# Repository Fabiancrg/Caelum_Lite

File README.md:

| Supported Targets | ESP32-C6 | ESP32-H2 |
| ----------------- |  -------- | -------- |

# Caelum - Zigbee Weather Station

## Project Description

This project implements a battery-powered environmental monitoring device using ESP32-C6/H2 with Zigbee connectivity. The device features a 3-endpoint design with remote sleep configuration, optimized for low-power operation with deep sleep support and extended wake time during network join.

This project is based on the examples provided in the ESP Zigbee SDK:

* [ESP Zigbee SDK Docs](https://docs.espressif.com/projects/esp-zigbee-sdk)
* [ESP Zigbee SDK Repo](https://github.com/espressif/esp-zigbee-sdk)

## Device Features

### 🌐 Zigbee Endpoints Overview

| Endpoint | Device Type | Clusters | Description |
|----------|-------------|----------|-------------|
| **1** | Environmental Sensor | Temperature, Humidity, Pressure | BME280 sensor via I2C |
| **2** | Rain Gauge | Analog Input | Tipping bucket rain sensor with rainfall totals |
| **3** | Sleep Configuration | Analog Input | Remote sleep duration control (60-7200 seconds) |

### 📋 Detailed Endpoint Descriptions

#### **Endpoint 1: Environmental Monitoring & Power Management**
- **Hardware**: BME280 sensor via I2C
  - **ESP32-H2**: SDA: GPIO10, SCL: GPIO11
  - **ESP32-C6**: SDA: GPIO6, SCL: GPIO7
- **Measurements**: 
  - 🌡️ **Temperature**: -40°C to +85°C (±1°C accuracy)
  - 💧 **Humidity**: 0-100% RH (±3% accuracy) 
  - 🌪️ **Pressure**: 300-1100 hPa (±1 hPa accuracy)
  - 🔋 **Battery Monitoring**: Li-Ion voltage (2.7V-4.2V) and percentage
- **Battery Monitoring**:
  - **Hardware**: GPIO4 (ADC1_CH4) with voltage divider (2x 100kΩ resistors)
  - **Voltage**: Real-time battery voltage in 0.1V units
  - **Percentage**: Battery level 0-100% based on Li-Ion discharge curve
  - **Calibration**: ESP32-H2 ADC correction factor (1.604x) for accurate readings
  - **Power Configuration Cluster**: Standard Zigbee battery attributes
- **Features**: Automatic reporting during wake cycles, Zigbee-standard units
- **Use Case**: Weather monitoring, HVAC automation, air quality tracking, battery-powered applications

#### **Endpoint 2: Rain Gauge System**
- **Hardware**: Tipping bucket rain gauge with reed switch
  - **ESP32-H2**: GPIO12 (RTC-capable for sleep wake-up)
  - **ESP32-C6**: GPIO5 (RTC-capable for sleep wake-up)
- **Measurements**: Cumulative rainfall in millimeters (0.36mm per tip)
- **Features**: 
  - Advanced debouncing (200ms + 1000ms bounce settle)
  - Persistent storage (NVS) for total tracking
  - Smart reporting (1mm threshold OR hourly)
  - Network-aware operation (only active when connected)
  - **Both targets**: Wake from deep sleep on rain detection
- **Specifications**: 
  - Maximum rate: 200mm/hour supported
  - Accuracy: ±0.36mm per bucket tip
  - Storage: Non-volatile total persistence across reboots
- **Use Case**: Weather station, irrigation control, flood monitoring

#### **Endpoint 3: Sleep Configuration**
- **Hardware**: Software-only (virtual endpoint)
- **Control**: Sleep duration in seconds (60-7200s range)
- **Features**:
  - Remote configuration via Zigbee2MQTT or Home Assistant
  - Persistent storage (NVS) - survives reboots
  - Real-time updates - changes apply on next wake cycle
  - Default: 900 seconds (15 minutes)
- **Use Case**: 
  - Battery optimization (longer intervals = longer battery life)
  - Seasonal adjustments (frequent updates in rainy season)
  - Dynamic power management based on weather conditions

### 🔧 Hardware Configuration

#### **Required Components**
- ESP32-C6 or ESP32-H2 development board
- BME280 environmental sensor module
- Tipping bucket rain gauge with reed switch
- Li-Ion battery (with protection circuit, 5V output recommended)
- Voltage divider (2x 100kΩ resistors for battery monitoring)
- Zigbee coordinator (ESP32-H2 or commercial gateway)

#### **Pin Assignments**

**ESP32-H2 (Recommended)**
```
GPIO 4  - Battery voltage input (ADC1_CH4 with voltage divider)
GPIO 10 - I2C SDA (BME280)
GPIO 11 - I2C SCL (BME280) 
GPIO 12 - Rain gauge input (RTC-capable)*
GPIO 9  - Built-in button (factory reset)
```

**ESP32-C6**
```
GPIO 4  - Battery voltage input (ADC1_CH4 with voltage divider)
GPIO 5  - Rain gauge input (RTC-capable)*
GPIO 6  - I2C SDA (BME280)
GPIO 7  - I2C SCL (BME280) 
GPIO 9  - Built-in button (factory reset)
```

*Both targets now use RTC-capable GPIO pins for rain detection during deep sleep

**Battery Voltage Divider Circuit**
```
Battery+ ──┬── 100kΩ ──┬── 100kΩ ── GND
           │           │
           │           └── GPIO4 (ADC input)
           │
           └── 5V output (to ESP32 power)
```
Note: Voltage divider monitors the cell voltage (2.7V-4.2V) while the battery pack provides 5V regulated output

### � Zigbee Integration
- **Protocol**: Zigbee 3.0  
- **Device Type**: End Device (sleepy end device for battery operation)
- **Supported Channels**: 11-26 (2.4 GHz)
- **Compatible**: Zigbee2MQTT, Home Assistant ZHA, Hubitat
- **OTA Support**: Over-the-air firmware updates enabled (see [OTA_GUIDE.md](OTA_GUIDE.md))

### ⚡ Power Management
- **Deep Sleep Mode**: Configurable intervals (60-7200 seconds, default 15 minutes)
  - **Configurable via Zigbee2MQTT**: Adjust sleep duration remotely from Home Assistant
  - **Connected**: Uses configured interval (default 15 minutes)
  - **Disconnected**: 30-second intervals for quick reconnection
  - **Max retries**: After 20 attempts (10 minutes), reduces to half configured duration
  - **Extended wake time**: Device stays awake for 60 seconds when not connected (instead of 10s) to allow Zigbee join process to complete
- **Wake-up Sources**:
  - Timer (configurable 60-7200 seconds)
  - **Rain detection during deep sleep** (both targets support RTC wake-up)
    - **ESP32-H2**: GPIO12 (RTC-capable)
    - **ESP32-C6**: GPIO5 (RTC-capable)
- **Network Retry Logic**: 
  - Prevents deep sleep when not connected to ensure reliable pairing
  - Extended 60-second wake period for join process completion
  - Connection success triggers 15-second reporting window before sleep
- **Battery Life**: Optimized for extended operation on battery power
- **Power Consumption**: ~100mA active, 7-10µA in deep sleep
- **Battery Estimate**: 3+ years with 2500mAh battery (15-minute intervals)

## 🚀 Quick Start

### Prerequisites

```bash
# Install ESP-IDF v5.5.1 or later
git clone -b v5.5.1 --recursive https://github.com/espressif/esp-idf.git
cd esp-idf
# For ESP32-H2 (recommended)
./install.sh esp32h2
# For ESP32-C6
./install.sh esp32c6
. ./export.sh
```

### Configure the Project
```bash
# For ESP32-H2 (recommended for better power management)
idf.py set-target esp32h2
# For ESP32-C6  
idf.py set-target esp32c6
idf.py menuconfig
```

### Build and Flash
```bash
# Erase previous data (recommended for first flash)
idf.py -p [PORT] erase-flash

# Build and flash the project
idf.py -p [PORT] flash monitor
```

### 🛠️ Configuration

### Device Operation

#### **Factory Reset**
- **Built-in Button (GPIO 9)**:
  - Long press (5s): Factory reset device

#### **Automatic Features**
- Environmental data reported during wake cycles
- Rain gauge totals stored persistently in NVS
- Smart rainfall reporting (1mm increments or hourly)
- Network connection status monitoring
- Deep sleep after data reporting (15-second window when connected, 60 seconds when not connected)
- Sleep duration remotely configurable via Zigbee2MQTT (60-7200 seconds)

### 📡 Data Reporting
- **Temperature/Humidity/Pressure**: Reported during wake cycles
- **Rainfall**: Immediate on tip detection (>1mm) or hourly
- **Sleep Duration**: Configurable 60-7200 seconds (default 15 minutes)
- **Sleep Cycle**: Configurable via Endpoint 3 for battery optimization

## 📊 Example Output

### Device Initialization
```
I (403) app_start: Starting scheduler on CPU0
I (408) WEATHER_STATION: Initialize Zigbee stack
I (558) WEATHER_STATION: Deferred driver initialization successful
I (568) WEATHER_STATION: BME280 sensor initialized successfully
I (578) WEATHER_STATION: Rain gauge initialized. Current total: 0.00 mm
I (578) WEATHER_STATION: Start network steering
```

### Network Connection
```
I (3558) WEATHER_STATION: Joined network successfully (Extended PAN ID: 74:4d:bd:ff:fe:63:f7:30, PAN ID: 0x13af, Channel:13, Short Address: 0x7c16)
I (3568) RAIN_GAUGE: Rain gauge enabled - device connected to Zigbee network
```

### Sensor Data Reporting
```
I (8000) WEATHER_STATION: 🌡️ Temperature: 22.35°C reported to Zigbee  
I (8010) WEATHER_STATION: 💧 Humidity: 45.20% reported to Zigbee
I (8020) WEATHER_STATION: 🌪️ Pressure: 1013.25 hPa reported to Zigbee
I (8030) BATTERY: 🔋 Li-Ion Battery: 4.17V (98%) - Zigbee values: 41 (0.1V), 196 (%*2)
I (8040) WEATHER_STATION: 📡 Temp: 22.4°C
I (8050) WEATHER_STATION: 📡 Humidity: 45.2%
I (8060) WEATHER_STATION: 📡 Pressure: 1013.3 hPa
```

### Rain Gauge Activity
```  
I (10000) RAIN_GAUGE: 🔍 Rain gauge interrupt received on GPIO18 (enabled: YES)
I (10010) RAIN_GAUGE: 🌧️ Rain pulse #1 detected! Total: 0.36 mm (+0.36 mm)
I (10020) RAIN_GAUGE: ✅ Rainfall total 0.36 mm reported to Zigbee
I (10030) WEATHER_STATION: 📡 Rain: 0.36 mm
```

### Deep Sleep Entry
```
I (18000) WEATHER_STATION: ⏳ Preparing for deep sleep...
I (18010) WEATHER_STATION: 💤 Entering deep sleep for 900 seconds (15 minutes)
```

## 🏠 Home Assistant Integration

When connected to Zigbee2MQTT or other Zigbee coordinators, the device appears as:

- **4x Sensor entities**: Temperature, Humidity, Pressure, Battery Percentage
- **1x Sensor entity**: Battery Voltage (mV)
- **1x Sensor entity**: Rainfall total with automatic updates
- **1x Number entity**: Sleep duration control (60-7200 seconds)

### Zigbee2MQTT Integration

A custom external converter is provided for full feature support with Zigbee2MQTT. See [ZIGBEE2MQTT_CONVERTER.md](ZIGBEE2MQTT_CONVERTER.md) for:
- Converter installation instructions
- Multi-endpoint support configuration
- Sleep duration control setup
- Home Assistant automation examples

### Device Information
- **Manufacturer**: ESPRESSIF
- **Model**: CAELUM-WS  
- **Firmware**: Configurable via CMakeLists.txt (default v0.1.0)
- **Supported**: Zigbee2MQTT with custom external converter

## 🔧 Configuration

Key parameters can be adjusted in `main/esp_zb_weather.h`:
- Default sleep duration: 900 seconds (15 minutes) - can be changed via Endpoint 3
- Sleep duration range: 60-7200 seconds (1 minute to 2 hours)
- Network retry interval: 30 seconds when disconnected
- Maximum connection retries: 20 attempts before reducing sleep interval
- Rain tip bucket volume: 0.36mm per tip
- Extended wake time: 60 seconds when not connected (for join process)

## 📝 Project Structure

```
WeatherStation/
├── main/
│   ├── esp_zb_weather.c     # Main Zigbee stack, 3-endpoint logic, network retry
│   ├── esp_zb_weather.h     # Configuration, endpoint definitions, firmware version
│   ├── esp_zb_ota.c         # OTA update implementation
│   ├── esp_zb_ota.h         # OTA interface
│   ├── sleep_manager.c      # Deep sleep management with RTC GPIO support
│   ├── sleep_manager.h      # Sleep manager interface
│   ├── bme280_app.c         # BME280 sensor driver with board-specific I2C
│   ├── bme280_app.h         # BME280 interface
│   ├── weather_driver.c     # DEPRECATED: Legacy driver (unused)
│   └── weather_driver.h     # DEPRECATED: Legacy interface (unused)
├── caelum-weather-station.js # Zigbee2MQTT external converter
├── CMakeLists.txt           # Build configuration with app_update dependency
├── partitions.csv           # Partition table with OTA support
├── sdkconfig.defaults       # Default SDK settings
├── OTA_GUIDE.md            # OTA update instructions
├── ZIGBEE2MQTT_CONVERTER.md # Zigbee2MQTT integration guide
├── DEEP_SLEEP_IMPLEMENTATION.md # Deep sleep implementation details
└── README.md               # This file
```

## 🔧 Troubleshooting

### Common Issues

#### **Rain Gauge Not Detecting**
- **ESP32-H2**: Verify GPIO12 connections and reed switch operation
- **ESP32-C6**: Verify GPIO5 connections and reed switch operation
- Check that device is connected to Zigbee network (rain gauge only active when connected)
- Ensure proper pull-down resistor on rain gauge input
- Both targets support rain detection during deep sleep

#### **BME280 Not Reading**  
- **ESP32-H2**: Check I2C connections (SDA: GPIO10, SCL: GPIO11)
- **ESP32-C6**: Check I2C connections (SDA: GPIO6, SCL: GPIO7)
- Verify BME280 I2C address (default: 0x76 or 0x77)
- Ensure proper power supply to sensor (3.3V)

#### **Battery Monitoring Issues**
- Verify voltage divider connections (2x 100kΩ resistors to GPIO4)
- Check battery cell voltage tap (should be 2.7V-4.2V at divider output)
- Ensure GPIO4 (ADC1_CH4) is properly configured
- Monitor serial output for ADC calibration messages
- **ESP32-H2 ADC quirk**: Uses empirical correction factor (1.604x) for DB_12 attenuation
- Battery percentage calculated from voltage (2.7V=0%, 4.2V=100%)

#### **Zigbee Connection Issues**
- Perform factory reset with long press (5s) on built-in button
- Ensure Zigbee coordinator is in pairing mode
- Check channel compatibility between coordinator and device
- **Auto-retry**: Device automatically retries every 30 seconds when disconnected
- **Extended wake time**: Device now stays awake for 60 seconds (instead of 10s) during join attempts
- **Battery impact**: Extended connection attempts may drain battery faster
- **Join timing**: Allow full 60 seconds for device to complete Zigbee join process

#### **Device Not Waking from Sleep**
- Check battery voltage (minimum 3.0V recommended)
- Verify wake-up sources (timer, rain gauge)
- Review sleep manager logs for errors
- **Network dependency**: Device stays awake longer when not connected to network

#### **High Battery Drain**
- Check if device is stuck in connection retry mode (30-second intervals)
- Verify Zigbee network is stable and accessible
- Monitor connection retry count in device logs
- Consider factory reset if connection issues persist

### 📋 Development Notes

- **ESP-IDF Version**: v5.5.1 recommended
- **Zigbee SDK**: Latest ESP Zigbee SDK required  
- **Memory Usage**: ~2MB flash, ~200KB RAM typical
- **Power Consumption**: ~100mA active, 7-10µA in deep sleep
- **Battery Operation**: Optimized for CR123A or Li-ion battery packs
- **Target Support**: Both ESP32-H2 and ESP32-C6 fully support RTC GPIO wake-up for rain detection

## 🔄 OTA Updates

This project supports Over-The-Air (OTA) firmware updates via Zigbee network. See [OTA_GUIDE.md](OTA_GUIDE.md) for detailed instructions on:
- Creating OTA images
- Configuring Zigbee2MQTT for OTA
- Performing updates
- Troubleshooting OTA issues

## 📄 License

This project follows dual licensing:
- **Software**: GNU General Public License v3.0 (see [LICENSE](LICENSE))
- **Hardware**: Creative Commons Attribution-NonCommercial-ShareAlike 4.0 (see [LICENSE-hardware](LICENSE-hardware))

## 🔄 Based On

This project is derived from ESP32 Zigbee SDK examples and implements a 3-endpoint architecture optimized for battery-powered weather station applications with:
- Remote sleep duration configuration (Endpoint 3)
- Deep sleep power management with network retry logic
- Extended wake time during Zigbee join process (60 seconds)
- RTC GPIO wake-up support for rain detection on both ESP32-H2 and ESP32-C6

## 🤝 Contributing

Contributions are welcome! Please feel free to submit issues or pull requests.

For technical queries, please open an issue on GitHub. Include:
- Complete serial monitor output
- Hardware configuration details  
- ESP-IDF and SDK versions
- Specific symptoms and reproduction steps

## 💖 Support

If you find this project useful, consider supporting the development:

---

**Project**: Caelum - ESP32 Zigbee Weather Station  
**Version**: Configurable via CMakeLists.txt (default v0.1.0)
**Compatible**: ESP32-C6, ESP32-H2, ESP-IDF v5.5.1+  
**License**: GPL v3 (Software) / CC BY-NC-SA 4.0 (Hardware)  
**Features**: 3-endpoint design, remote sleep config, OTA updates, RTC wake-up

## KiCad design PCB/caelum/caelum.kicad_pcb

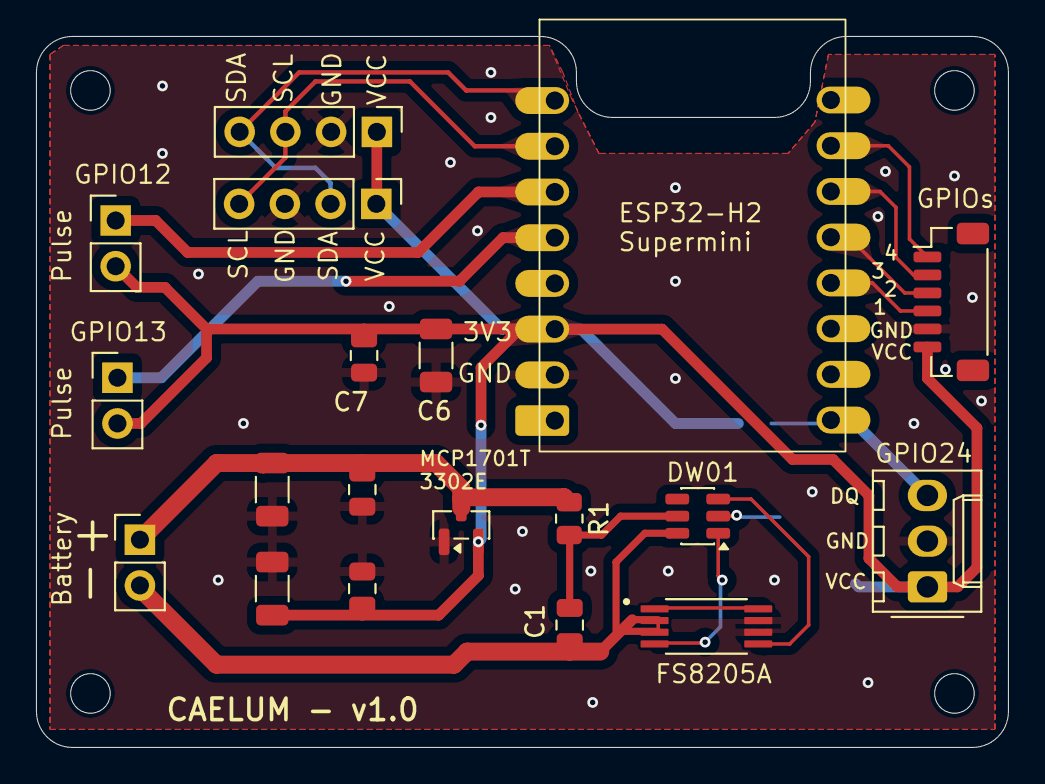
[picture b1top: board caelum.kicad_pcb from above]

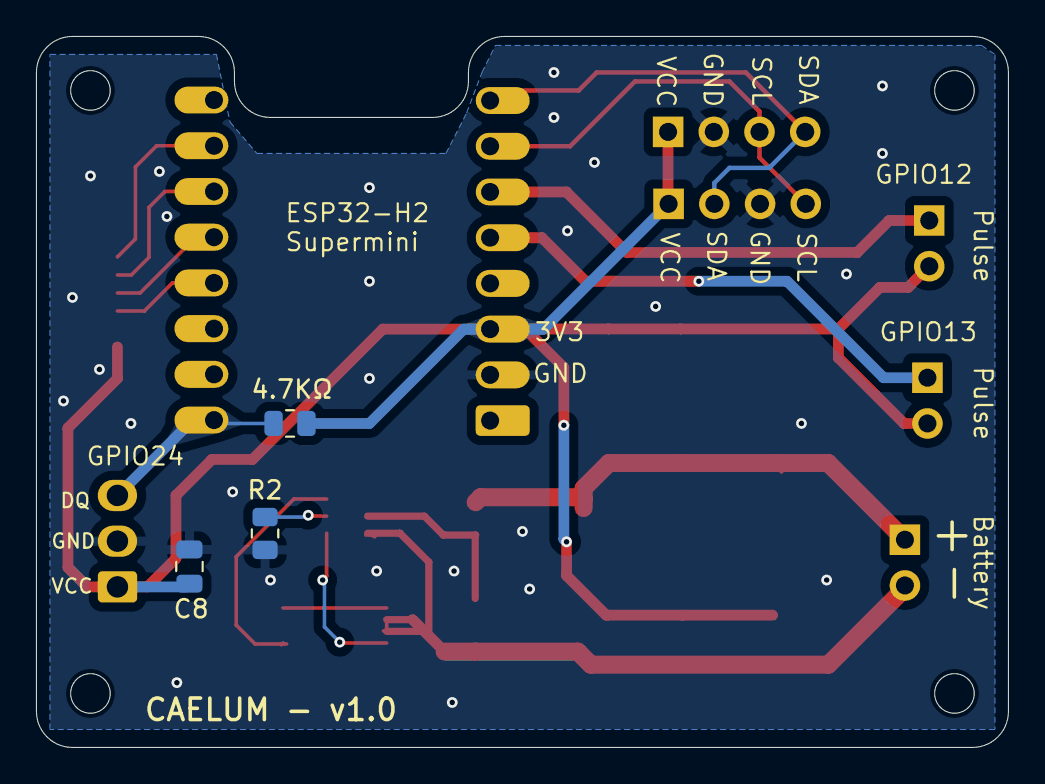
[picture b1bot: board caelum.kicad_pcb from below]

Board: 2 copper layers, 54.0 x 39.5 mm, 26 parts (3 on the bottom side), 18 nets.

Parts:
C1, C3, C5, C7, C8: 0.1µF; C_0805_2012Metric
C2, C4, C6: 1µF; C_1206_3216Metric
H1, H2, H3, H4: MountingHole; MountingHole_2.2mm_M2
J1: Conn_01x06_Pin; JST_SH_BM06B-SRSS-TB_1x06-1MP_P1.00mm_Vertical
J3: Pulse1; PinHeader_1x02_P2.54mm_Vertical
J4: Batt; PinHeader_1x02_P2.54mm_Vertical
J6: Pulse2; PinHeader_1x02_P2.54mm_Vertical
J7, J10: Conn_01x04_Pin; PinHeader_1x04_P2.54mm_Vertical
J8: DS18B20; Molex_KK-254_AE-6410-03A_1x03_P2.54mm_Vertical
Q1: FS8205A-FC; SOP65P640X120-8N-FC
R1: 100R; R_0805_2012Metric
R2: 1K; R_0805_2012Metric
R3: 4.7K; R_0805_2012Metric
U1: DW01A; SOT-23-6
U2: MCP1700T-3302E; SOT-23
U3: ESP32-H2-SUPERMINI; ESP32H2-Supermini

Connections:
+3V3: C4.2, C5.2, C6.1, C7.1, C8.2, J1.6, J3.2, J6.2, J7.1, J8.1, J10.1, R3.1, U2.2 (VO), U3.7 (3V3)
BATT+: C2.1, C3.1, J4.1, R1.1, U2.3 (VI)
BATT-: C1.2, J4.2, Q1.2 (S1), Q1.3 (S1), U1.6 (GND)
GPIO1: J1.4, U3.16 (IO1)
GPIO2: J1.3, U3.15 (IO2)
GPIO3: J1.2, U3.14 (IO3)
GPIO4: J1.1, U3.13 (IO4)
GPIO12: J3.1, U3.4 (IO12)
GPIO13: J6.1, U3.5 (IO13)
GPIO24: J8.3, R3.2, U3.19 (IO24)
unnamed: Q1.1 (D12), Q1.8 (D12)
unnamed: Q1.4 (G1), U1.1 (OD)
unnamed: Q1.5 (G2), U1.3 (OC)
unnamed: R2.1, U1.2 (CS)
unnamed: C1.1, R1.2, U1.5 (VCC)
OUT-: C2.2, C3.2, C4.1, C5.1, C6.2, C7.2, C8.1, J1.5, J7.3, J8.2, J10.2, Q1.6 (S2), Q1.7 (S2), R2.2, U2.1 (GND), U3.8 (GND)
SCL: J7.4, J10.3, U3.3 (IO11)
SDA: J7.2, J10.4, U3.2 (IO10)

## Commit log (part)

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2025-10-16 Project creation
2025-11-06 Add battery monitoring functionality: implement battery voltage and percentage reporting, and refine ADC calibration for ESP32-H2
2025-11-06 Update README to enhance battery monitoring section: clarify endpoint descriptions, add calibration details, and improve voltage divider circuit explanation
2025-11-06 Update project version to 1.1.10, enhance OTA support, and optimize battery reading logic
2025-11-06 Enhance LED debug control logging for Zigbee messages
2025-11-10 Refactor code structure for improved readability and maintainability + Add KiCad PCB project
2025-11-11 Update sdkconfig for light sleep features
2025-11-11 Refactor LED control logic for improved power management during network operations. Deinitialize LED after successful join to save power, and update LED behavior for connection states. Remove unused 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
2025-11-12 Refactor rain gauge and sleep configuration handling. Remove sleep duration reporting and configuration endpoint to streamline Zigbee operations. Update reporting intervals for rain gauge and battery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
2025-11-12 Refactor LED control logic for improved power management during network operations. Deinitialize LED after successful join to save power and update LED behavior for connection states.
2025-11-12 Update project version to 1.5 and reset build number to 0. Modify rain gauge task to save rainfall data on every pulse to prevent data loss during unexpected reboots.
2025-11-13 Add AHT20 and BMP280 sensor support
    - Implemented AHT20 sensor driver with initialization, measurement triggering, and data reading functions.
    - Implemented BMP280 sensor driver with initialization, measurement triggering, and data reading functions.
    - Updated sensor interface to support detection and interaction with AHT20 and BMP280 sensors.
    - Enhanced I2C bus scanning for better device detection and debugging.
    - Updated sdkconfig to enable necessary configurations for new sensors.
2025-11-15 Update project version to 1.7 and reset build number to 0. Add timeout handling in button task to prevent infinite loops.
2025-12-04 feat: Enhance Caelum Weather Station functionality and configuration
    - Updated PCB configuration to set active layer to 0 and adjusted column widths for better layout.
    - Expanded device endpoints in the weather station to include additional sensors (pulse counter and temperature).
    - Implemented sleep prevention during initial network configuration to ensure proper reporting setup.
    - Added logic to load and save pulse counter data to RTC and NVS for persistence across power cycles.
    - Improved DS18B20 sensor initialization with retry logic for better reliability.
    - Enhanced logging for various operations to provide clearer insights during execution.
2025-12-14 fix: Reset column widths in net inspector panel to default values
2025-12-18 Add files for PCB and schematic in caelum_v2
2025-12-18 Move PCB V2 to new project
2025-12-26 Update BMP280 driver: add raw ADC reading functions and improve pressure reading logic
2025-12-27 Update build number to 40 and enhance Zigbee lock handling with timeouts
2025-12-28 Update build number to 50 and improve BMP280 pressure conversion handling with busy-wait
2025-12-29 Add logging to flash to debug crashes
2025-12-29 Implement feature X to enhance user experience and optimize performance
2026-03-14 Refactor esp_zb_weather.c to remove persistent logging and optimize power management settings
2026-03-14 Update project version to 2.1 and enhance OTA logging with total image size
2026-03-14 Fix OTA image size handling and update logging level in sdkconfig
2026-03-14 Improve ESP32 magic byte search logic in Zigbee OTA handler to account for header offset
2026-03-14 bump to version 2.1.10 to test OTA
2026-03-14 Update version to 2.1.40, enhance OTA handling, and adjust logging levels
2026-03-14 Update build number to 60 and refine OTA handling in esp_zb_ota and esp_zb_weather
2026-03-14 Enhance sensor handling and logging: update humidity endpoint, add initial sensor read trigger, and handle NaN/Inf values in RTC data
2026-03-15 Update version to 2.2, reset build number, and adjust logging configurations
2026-03-15 Enable USB Serial/JTAG support and configure console settings
2026-03-15 Add GPIO ISR service installation check and improve logging levels in sdkconfig
2026-03-15 Update USB Serial/JTAG configuration and adjust logging levels in sdkconfig
2026-03-15 Refactor OTA upgrade handling and improve logging for chunk processing
2026-03-15 Update logging levels and enable USB Serial/JTAG support in sdkconfig
2026-03-15 Enable USB Serial/JTAG support and adjust logging levels in sdkconfig
2026-04-18 Add PM lock for initial configuration to prevent sleep during network join
2026-04-19 Refactor Zigbee reporting configuration to eliminate lock acquisition
    - Removed unnecessary lock acquisition for rain gauge and pulse counter reporting configuration, as these are now called from the Zigbee task context.
    - Updated the battery read and report function to include lock acquisition for attribute updates.
    - Adjusted the handling of attribute updates for DS18B20, rain gauge, and pulse counter to ensure proper locking mechanisms are in place.
    - Modified sdkconfig to change console settings and improve UART configurations.
    - Added boot log to capture detailed startup information and error handling.
2026-04-19 Add critical section protection for DS18B20 1-Wire communication to prevent interrupt preemption

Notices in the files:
README.md:
License: CC BY-NC-SA 4.0
